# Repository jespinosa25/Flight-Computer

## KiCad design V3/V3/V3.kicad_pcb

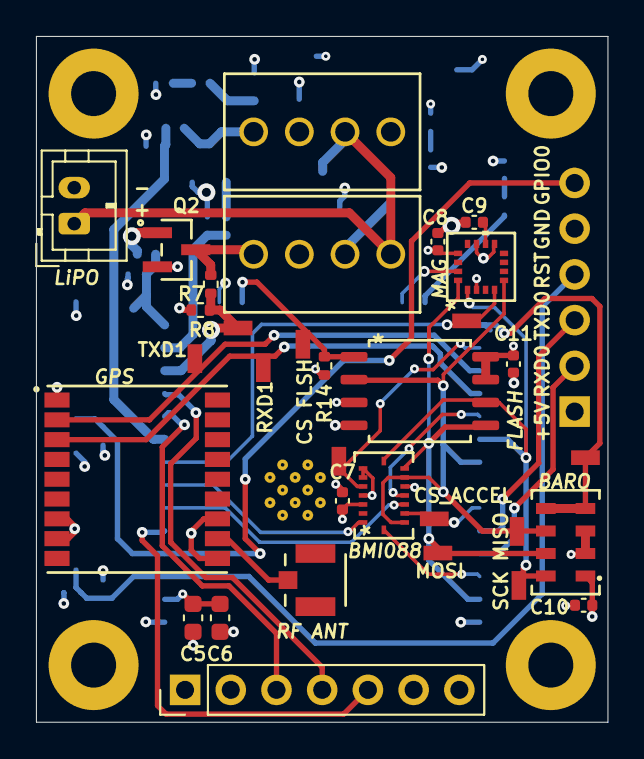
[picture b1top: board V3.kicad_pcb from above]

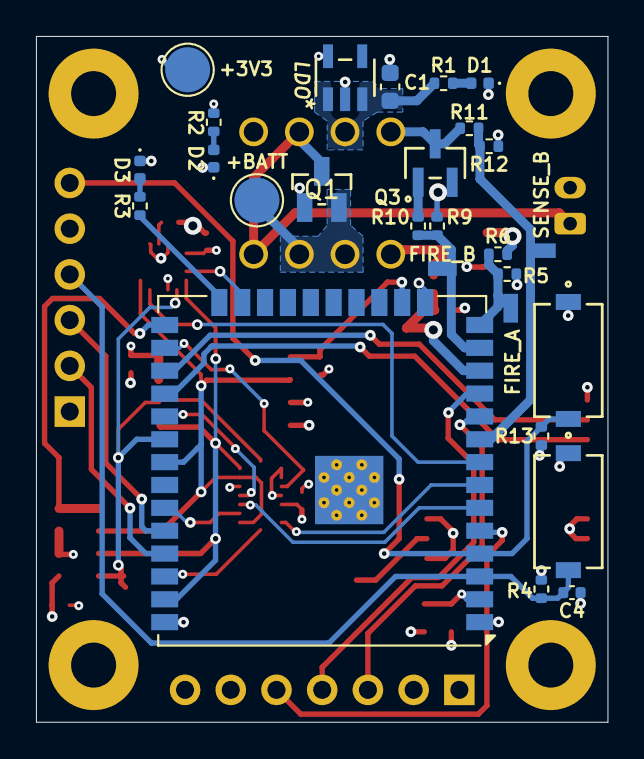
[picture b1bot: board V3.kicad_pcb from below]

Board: 4 copper layers, 31.8 x 38.1 mm, 64 parts (28 on the bottom side), 40 nets.

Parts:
+3V3: TestPoint; TestPoint_Pad_D2.5mm
+BATT: TestPoint; TestPoint_Pad_D2.5mm
BARO: MS560702BA03-50; SON8_MS5611_TEC
BMI088
: BMI088; QFN_BMI085_BOS
BT1: LiPO; JST_PH_B2B-PH-K_1x02_P2.00mm_Vertical
C1: 22uF; C_0603_1608Metric
C4, C8: 1uF; C_0402_1005Metric
C5: 10uF; C_0603_1608Metric
C6: 0.1uF; C_0603_1608Metric
C7, C10, C11: 0.1uF; C_0402_1005Metric
C9: 10uF; C_0402_1005Metric
D1: RED; LED_0402_1005Metric
D2: GREEN; LED_0402_1005Metric
D3: BLUE; LED_0402_1005Metric
FLASH: W25Q16JVSSIQ; W25Q16JVSSIQ_WIN
GPS: MAX-M10M-00B; MOD18_MAX-M10M_UBL
H1, H2, H3, H4: MountingHole_Pad; MountingHole_2.5mm_Pad
J1, J2: Conn_01x04_Pin; CONN_1725672_PXC
J3: Conn_01x06_Pin; PinSocket_1x06_P2.54mm_Vertical
J4: Conn_01x07_Pin; PinHeader_1x07_P2.54mm_Vertical
J5: 2337019-1; CONN_2337019-1_TEC
LDO: LD2980ABM33TR; SOT23-5L_STM
MAG: MMC5983MA; MMC5983MA_MEM
Q1: DMP3099L-7; DMP3099L-7_DIO
Q2, Q3: NMOS; SOT-23_MCC-M
R1: 110; R_0402_1005Metric
R2, R3: 50; R_0402_1005Metric
R4, R13, R14: 10k; R_0402_1005Metric
R5, R7, R9, R11: 100k; R_0402_1005Metric
R6, R10: 1k; R_0402_1005Metric
R8, R12: 27k; R_0402_1005Metric
SW1, SW2: PTS636 SM50J SMTR LFS; SW_PTS636_CNK
TP3, TP4, TP5, TP6, TP7, TP8, TP9, TP10, TP11, TP12, TP13, TP14, TP16, TP17: TestPoint; CONN1_RCU-0C_TEC
U3: ESP32-WROOM-32UE

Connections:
+3.3V: +3V3.1, BARO.1 (VDD), BMI088.3 (VDD), BMI088.11 (VDDIO), C5.1, C6.1, C7.1, C8.1, C10.2, C11.1, FLASH.3 (/WP_(IO2)), FLASH.7 (HOLD), FLASH.8 (VIN), GPS.7 (V_IO), GPS.8 (VCC), J4.6, LDO.5 (VOUT), MAG.2 (VDD), MAG.13 (VDDIO), R2.1, R4.2, R13.2, R14.2, U3.2 (VDD)
+BATT: +BATT.1, C1.1, J1.2, J1.3, J2.3, LDO.1 (VIN), LDO.3 (INHIBIT), Q1.2 (S), R1.1
ACCEL_INT_A: BMI088.16 (INT1), U3.36 (IO22)
ACCEL_INT_B: BMI088.1 (INT2), U3.7 (IO35)
CS_ACCEL: BMI088.14 (CSB1), TP10.1, U3.33 (IO21)
CS_BARO: BARO.4 (CSB), BARO.5 (CSB), TP12.1, U3.25 (IO0)
CS_FLASH: FLASH.1 (CS), R14.1, TP14.1, U3.16 (IO13)
CS_GYRO: BMI088.5 (CSB2), TP11.1, U3.26 (IO4)
CS_MAG: MAG.4 (SPI_CS), TP13.1, U3.8 (IO32)
FIRE_A: R5.1, R6.1, TP6.1, U3.14 (IO12)
FIRE_B: R9.1, R10.1, TP7.1, U3.13 (IO14)
GND: BARO.2 (PS), BARO.3 (GND), BMI088.4 (GNDA), BMI088.6 (GNDIO), BMI088.7 (PS), BT1.2 (-), C1.2, C4.2, C5.2, C6.2, C7.2, C8.2, C9.2, C10.1, C11.2, D1.1 (K), D2.1 (K), D3.1 (K), FLASH.4 (GND), GPS.1 (GND), GPS.10 (GND), GPS.12 (GND), H1.1, H2.1, H3.1, H4.1, J2.1, J3.5, J4.1, J4.2, J4.7, LDO.2 (GND), MAG.9 (GND), MAG.11 (GND), Q1.1 (G), Q2.2 (S), Q3.2 (S), R5.2, R8.1, R9.2, R12.1, SW1.1, SW2.1, U3.1 (GND), U3.15 (GND), U3.38 (GND), U3.39 (GND)
GPIO_0: J3.6, R13.1, SW2.2, U3.4 (SENSOR_VP)
GYRO_INT_A: BMI088.12 (INT3), U3.29 (IO5)
GYRO_INT_B: BMI088.13 (INT4), U3.6 (IO34)
MAG_INT: MAG.15 (INT), U3.23 (IO15)
MISO: BARO.6 (SDO), BMI088.10 (SDO2), BMI088.15 (SDO1), FLASH.2 (DO_(IO1)), MAG.5 (SPI_SDO), TP3.1, U3.31 (IO19)
MOSI: BARO.7 (SDI/SDA), BMI088.9 (SDA/SDI), FLASH.5 (DI_(IO0)), MAG.16 (SDA/SPI_SDI), TP4.1, U3.37 (IO23)
MOS_A: J1.4, Q2.3 (D), R7.2
MOS_B: J2.4, Q3.3 (D), R11.2
unnamed: D1.2 (A), R1.2
unnamed: D2.2 (A), R2.2
unnamed: D3.2 (A), R3.2
unnamed: Q2.1 (G), R6.2
unnamed: Q3.1 (G), R10.2
unnamed: GPS.11 (RF_IN), J5.1
unnamed: C9.1, MAG.10 (CAP)
PROGRAM_LED: R3.1, U3.24 (IO2)
RAW_BATT: BT1.1 (+), J1.1, J2.2, Q1.3 (D)
RESET: C4.1, J3.4, R4.1, SW1.2, U3.3 (EN)
RF_INT: J4.5, U3.5 (SENSOR_VN)
RXD0: J3.2, U3.35 (TXD0/IO1)
RXD1: GPS.3 (RXD), TP8.1, U3.28 (IO17)
RXD2: J4.3, U3.10 (IO25)
SCK: BARO.8 (SCLK), BMI088.8 (SCL/SCK), FLASH.6 (CLK), MAG.1 (SCL/SPI_SCK), TP5.1, U3.30 (IO18)
SENSE_A: R7.1, R8.2, TP16.1, U3.12 (IO27)
SENSE_B: R11.1, R12.2, TP17.1, U3.9 (IO33)
TXD0: J3.3, U3.34 (RXD0/IO3)
TXD1: GPS.2 (TXD), TP9.1, U3.27 (IO16)
TXD2: J4.4, U3.11 (IO26)

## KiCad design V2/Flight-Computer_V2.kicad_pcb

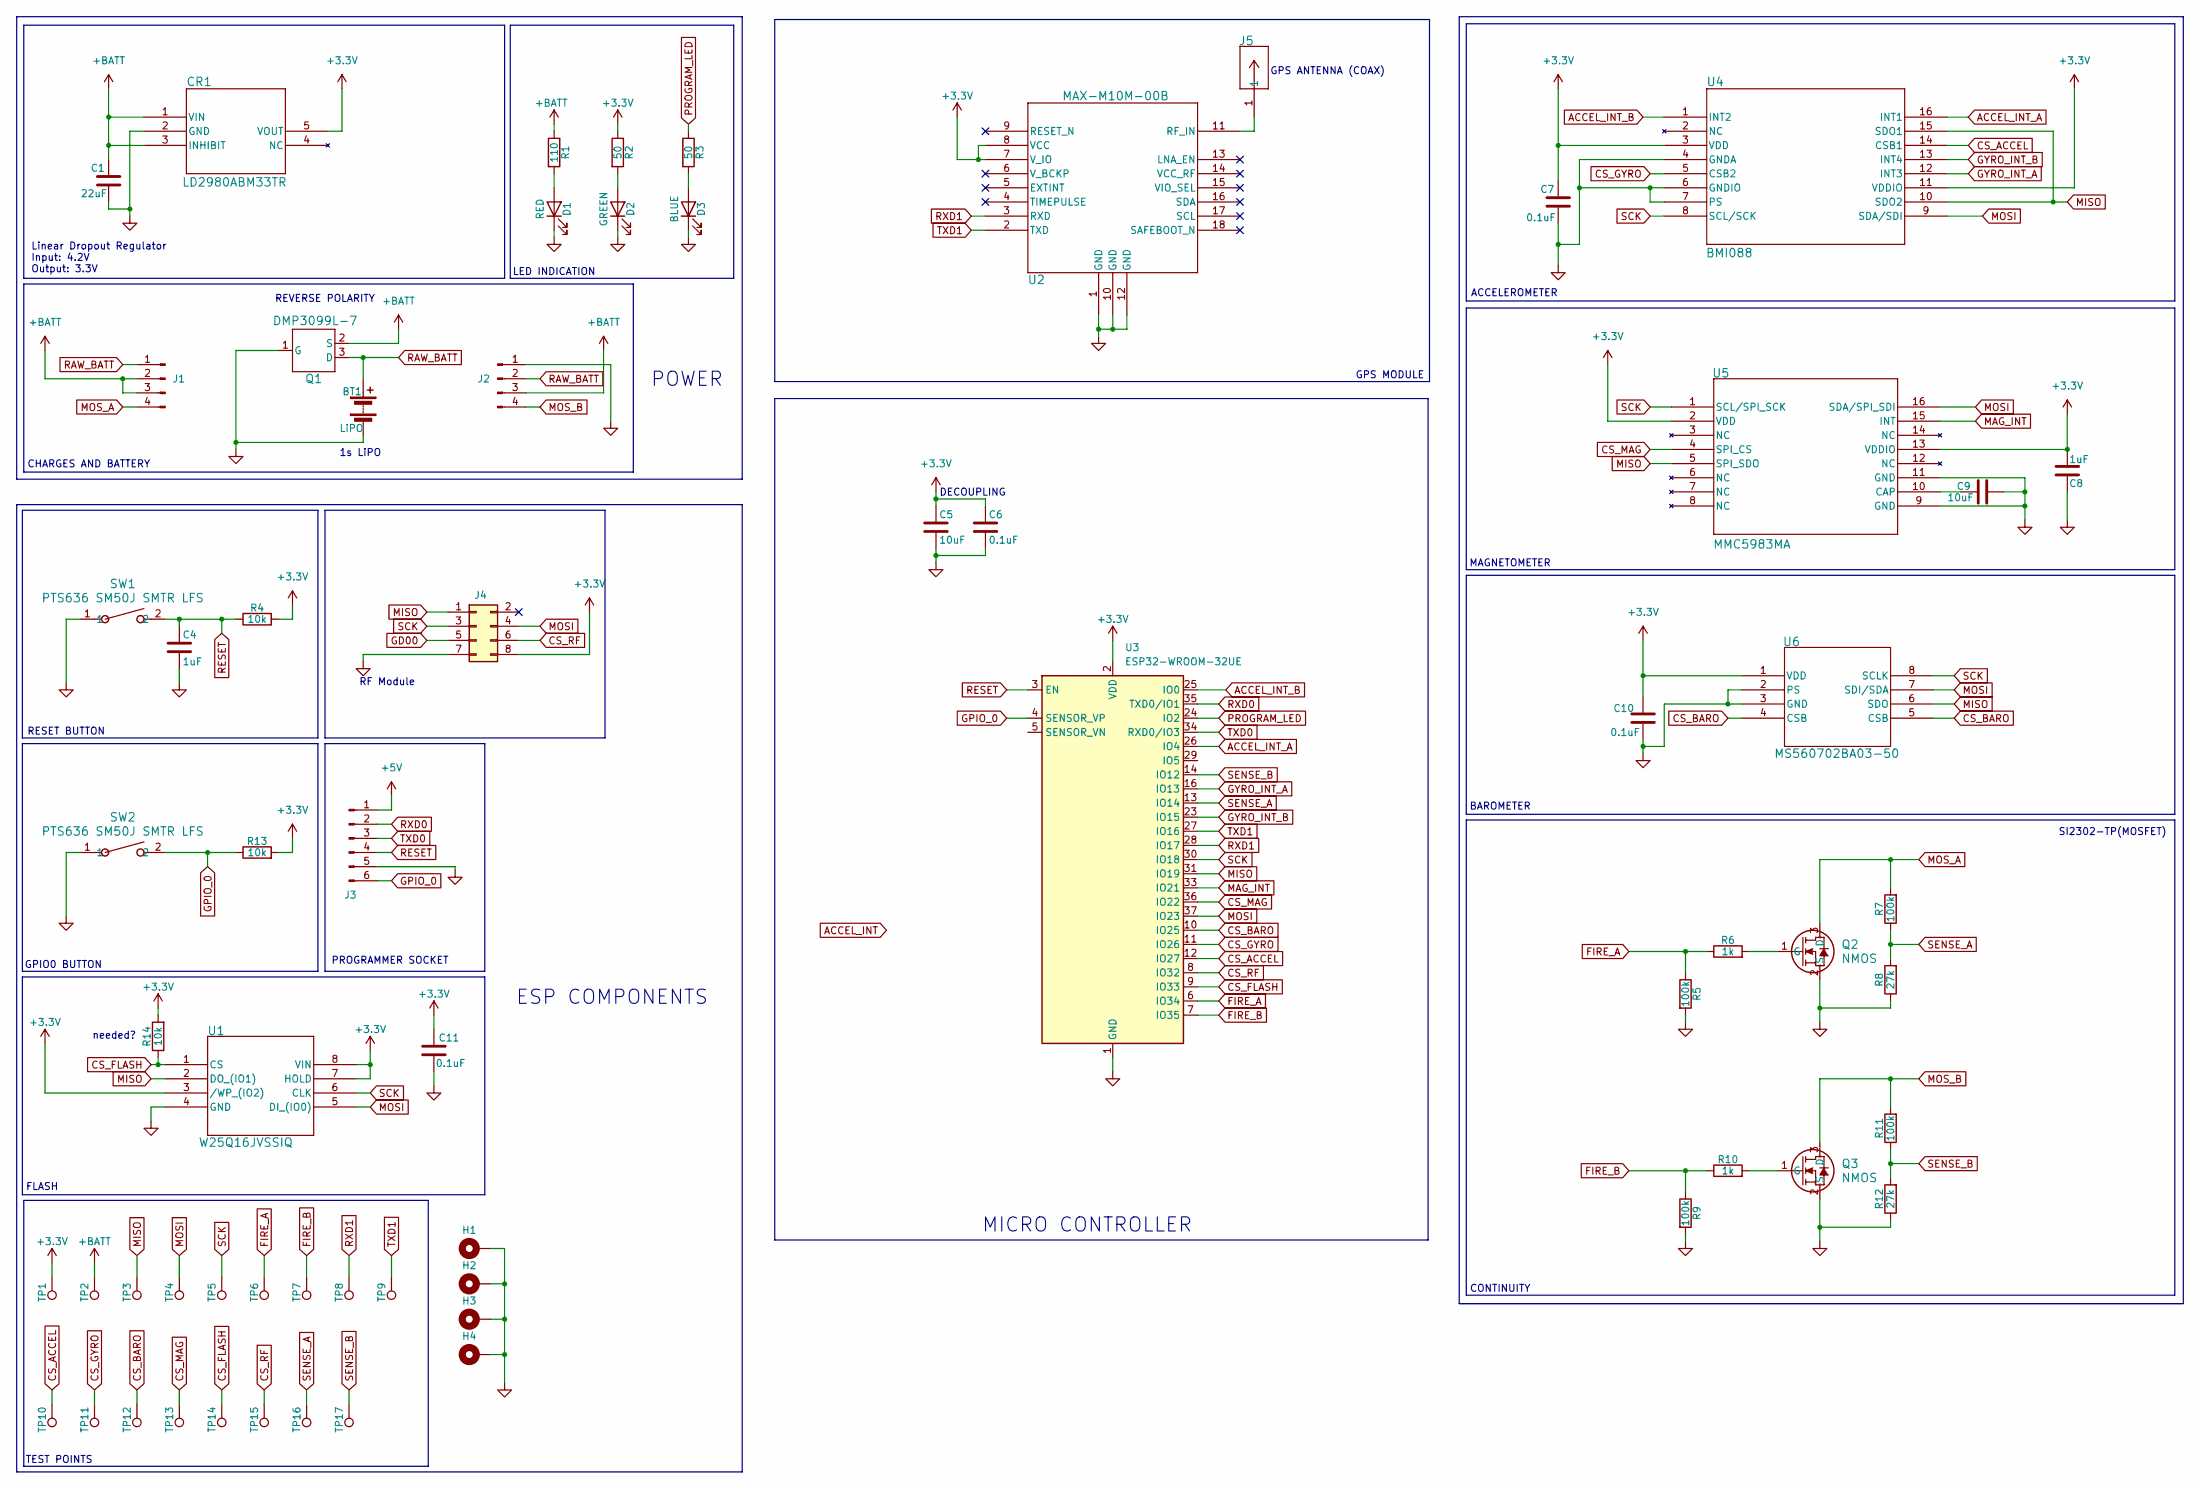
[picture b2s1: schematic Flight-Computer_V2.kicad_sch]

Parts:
BT1: LiPO; JST_PH_B2B-PH-K_1x02_P2.00mm_Vertical
C1: 22uF; C_0603_1608Metric
C4, C8: 1uF; C_0402_1005Metric
C5: 10uF; C_0603_1608Metric
C6: 0.1uF; C_0603_1608Metric
C7, C10, C11: 0.1uF; C_0402_1005Metric
C9: 10uF; C_0402_1005Metric
CR1: LD2980ABM33TR; SOT23-5L_STM
D1: RED; LED_0402_1005Metric
D2: GREEN; LED_0402_1005Metric
D3: BLUE; LED_0402_1005Metric
H1, H2, H3, H4: MountingHole_Pad; MountingHole_2.5mm_Pad
J1, J2: Conn_01x04_Pin; CONN_1725672_PXC
J3: Conn_01x06_Pin; PinSocket_1x06_P2.54mm_Vertical
J4: Conn_02x04_Odd_Even; PinSocket_2x04_P2.54mm_Vertical
J5: 2337019-1; CONN_2337019-1_TEC
Q1: DMP3099L-7; DMP3099L-7_DIO
Q2, Q3: NMOS; SOT-23_MCC-M
R1: 110; R_0402_1005Metric
R2, R3: 50; R_0402_1005Metric
R4, R13, R14: 10k; R_0402_1005Metric
R5, R7, R9, R11: 100k; R_0402_1005Metric
R6, R10: 1k; R_0402_1005Metric
R8, R12: 27k; R_0402_1005Metric
SW1, SW2: PTS636 SM50J SMTR LFS; SW_PTS636_CNK
TP1, TP2: TestPoint; TestPoint_Pad_D2.5mm
TP3, TP4, TP5, TP6, TP7, TP8, TP9, TP10, TP11, TP12, TP13, TP14, TP15, TP16, TP17: TestPoint; TestPoint_Loop_D2.60mm_Drill1.6mm_Beaded
U1: W25Q16JVSSIQ; W25Q16JVSSIQ_WIN
U2: MAX-M10M-00B; MOD18_MAX-M10M_UBL
U3: ESP32-WROOM-32UE
U4: BMI088; QFN_BMI085_BOS
U5: MMC5983MA; MMC5983MA_MEM
U6: MS560702BA03-50; SON8_MS5611_TEC

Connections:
+3.3V: C5.1, C6.1, C7.1, C8.1, C10.2, C11.1, CR1.5 (VOUT), J4.8, R2.1, R4.2, R13.2, R14.2, TP1.1, U1.3 (/WP_(IO2)), U1.7 (HOLD), U1.8 (VIN), U2.7 (V_IO), U2.8 (VCC), U3.2 (VDD), U4.3 (VDD), U4.11 (VDDIO), U5.2 (VDD), U5.13 (VDDIO), U6.1 (VDD)
+5V: J3.1
+BATT: C1.1, CR1.1 (VIN), CR1.3 (INHIBIT), J1.2, J1.3, J2.3, Q1.2 (S), R1.1, TP2.1
ACCEL_INT_A: U3.26 (IO4), U4.16 (INT1)
ACCEL_INT_B: U3.25 (IO0), U4.1 (INT2)
CS_ACCEL: TP10.1, U3.12 (IO27), U4.14 (CSB1)
CS_BARO: TP12.1, U3.10 (IO25), U6.4 (CSB), U6.5 (CSB)
CS_FLASH: R14.1, TP14.1, U1.1 (CS), U3.9 (IO33)
CS_GYRO: TP11.1, U3.11 (IO26), U4.5 (CSB2)
CS_MAG: TP13.1, U3.36 (IO22), U5.4 (SPI_CS)
CS_RF: J4.6, TP15.1, U3.8 (IO32)
FIRE_A: R5.1, R6.1, TP6.1, U3.6 (IO34)
FIRE_B: R9.1, R10.1, TP7.1, U3.7 (IO35)
GD00: J4.5
GND: BT1.2 (-), C1.2, C4.2, C5.2, C6.2, C7.2, C8.2, C9.2, C10.1, C11.2, CR1.2 (GND), D1.1 (K), D2.1 (K), D3.1 (K), H1.1, H2.1, H3.1, H4.1, J2.1, J3.5, J4.7, Q1.1 (G), Q2.2 (S), Q3.2 (S), R5.2, R8.1, R9.2, R12.1, SW1.1, SW2.1, U1.4 (GND), U2.1 (GND), U2.10 (GND), U2.12 (GND), U3.1 (GND), U3.15 (GND), U3.38 (GND), U3.39 (GND), U4.4 (GNDA), U4.6 (GNDIO), U4.7 (PS), U5.9 (GND), U5.11 (GND), U6.2 (PS), U6.3 (GND)
GPIO_0: J3.6, R13.1, SW2.2, U3.4 (SENSOR_VP)
GYRO_INT_A: U3.16 (IO13), U4.12 (INT3)
GYRO_INT_B: U3.23 (IO15), U4.13 (INT4)
MAG_INT: U3.33 (IO21), U5.15 (INT)
MISO: J4.1, TP3.1, U1.2 (DO_(IO1)), U3.31 (IO19), U4.10 (SDO2), U4.15 (SDO1), U5.5 (SPI_SDO), U6.6 (SDO)
MOSI: J4.4, TP4.1, U1.5 (DI_(IO0)), U3.37 (IO23), U4.9 (SDA/SDI), U5.16 (SDA/SPI_SDI), U6.7 (SDI/SDA)
MOS_A: J1.4, Q2.3 (D), R7.2
MOS_B: J2.4, Q3.3 (D), R11.2
unnamed: D1.2 (A), R1.2
unnamed: D2.2 (A), R2.2
unnamed: D3.2 (A), R3.2
unnamed: Q2.1 (G), R6.2
unnamed: Q3.1 (G), R10.2
unnamed: J5.1, U2.11 (RF_IN)
unnamed: C9.1, U5.10 (CAP)
PROGRAM_LED: R3.1, U3.24 (IO2)
RAW_BATT: BT1.1 (+), J1.1, J2.2, Q1.3 (D)
RESET: C4.1, J3.4, R4.1, SW1.2, U3.3 (EN)
RXD0: J3.2, U3.35 (TXD0/IO1)
RXD1: TP8.1, U2.3 (RXD), U3.28 (IO17)
SCK: J4.3, TP5.1, U1.6 (CLK), U3.30 (IO18), U4.8 (SCL/SCK), U5.1 (SCL/SPI_SCK), U6.8 (SCLK)
SENSE_A: R7.1, R8.2, TP16.1, U3.13 (IO14)
SENSE_B: R11.1, R12.2, TP17.1, U3.14 (IO12)
TXD0: J3.3, U3.34 (RXD0/IO3)
TXD1: TP9.1, U2.2 (TXD), U3.27 (IO16)

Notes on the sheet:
BAROMETER
LED INDICATION
1s LiPO
TEST POINTS
PROGRAMMER SOCKET
GPS ANTENNA (COAX)
ACCELEROMETER
needed?
RF Module
Linear Dropout Regulator Input: 4.2V Output: 3.3V
GPS MODULE
ESP COMPONENTS
FLASH
GPIO0 BUTTON
POWER
RESET BUTTON
CONTINUITY
SI2302-TP(MOSFET)
DECOUPLING
REVERSE POLARITY
CHARGES AND BATTERY
MAGNETOMETER
MICRO CONTROLLER

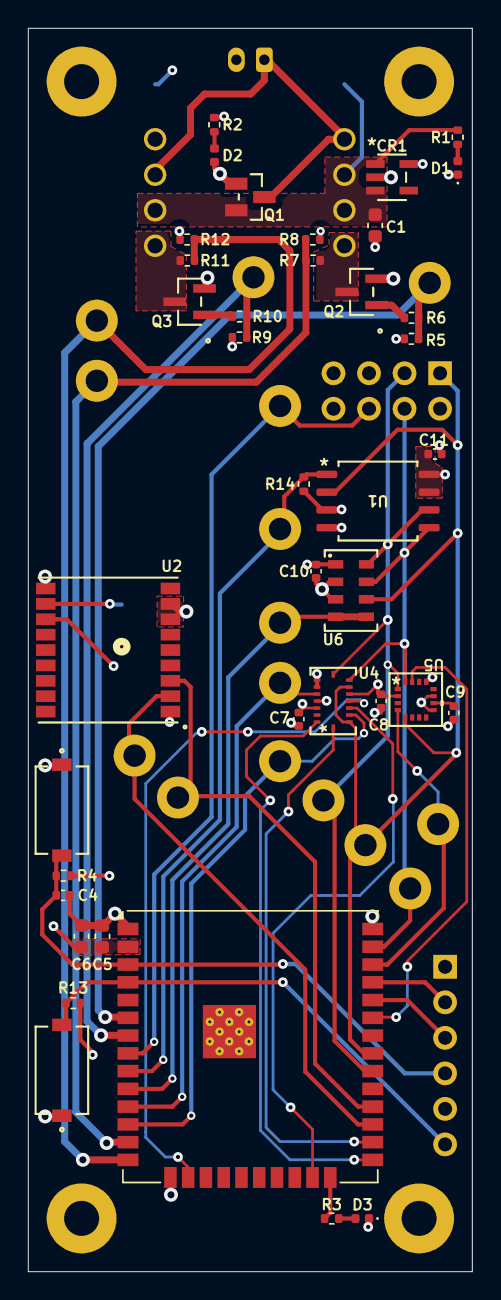
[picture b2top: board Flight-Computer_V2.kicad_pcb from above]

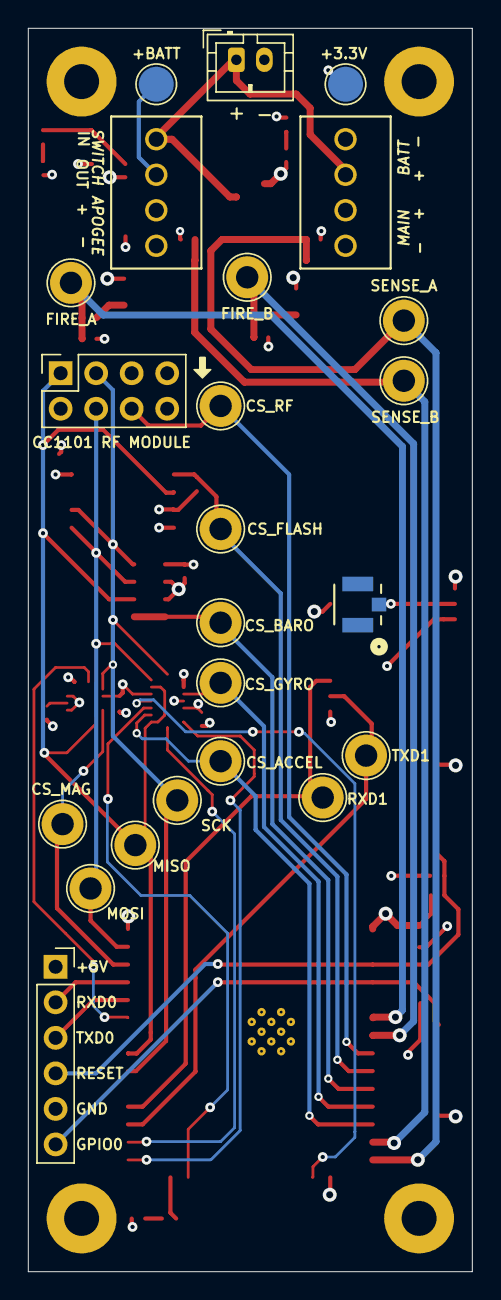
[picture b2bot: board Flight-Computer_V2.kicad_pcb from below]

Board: 4 copper layers, 31.8 x 88.9 mm, 65 parts (23 on the bottom side), 38 nets.

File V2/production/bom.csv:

Designator,Footprint,Quantity,Value,LCSC Part #
BT1,JST_PH_B2B-PH-K_1x02_P2.00mm_Vertical,1,LiPO,
C1,0201,1,22uF,
"C10, C11, C6, C7",0201,4,0.1uF,
"C4, C8",0201,2,1uF,
"C5, C9",0201,2,10uF,
CR1,SOT23-5L_STM,1,LD2980ABM33TR,
D1,0201,1,RED,
D2,0201,1,GREEN,
D3,0201,1,BLUE,
GPS_ANT,Pin_D1.0mm_L10.0mm,1,Pin_D1.0mm_L10.0mm,
IC1,ESP32S2MINI2N4R2,1,ESP32-S2-MINI-2-N4R2,
"J1, J2",CONN_1725672_PXC,2,Conn_01x04_Pin,
J3,PinSocket_1x06_P2.54mm_Vertical,1,Conn_01x06_Pin,
J4,PinSocket_2x04_P2.54mm_Vertical,1,Conn_02x04_Odd_Even,
Q1,DMP3099L-7_DIO,1,PMOS,
"Q2, Q3",SOT-23_MCC,2,NMOS,
R1,0201,1,110,
"R10, R6",0201,2,1k,
"R11, R5, R7, R9",0201,4,100k,
"R12, R8",0201,2,27k,
"R2, R3",0201,2,50,
R4,0201,1,10k,
SW1,SW_PTS636_CNK,1,PTS636 SM50J SMTR LFS,
"TP1, TP2",TestPoint_Pad_D2.5mm,2,TestPoint,
"TP10, TP11, TP12, TP14, TP15, TP3, TP4, TP5, TP6, TP7, TP8, TP9",TestPoint_Loop_D1.80mm_Drill1.0mm_Beaded,12,TestPoint,
U1,W25Q16JVSSIQ_WIN,1,W25Q16JVSSIQ,
U2,MOD18_MAX-M10M_UBL,1,MAX-M10M-00B,
U4,QFN_BMI085_BOS,1,BMI088,
U5,MMC5983MA_MEM,1,MMC5983MA,
U6,SON8_MS5611_TEC,1,MS560702BA03-50,

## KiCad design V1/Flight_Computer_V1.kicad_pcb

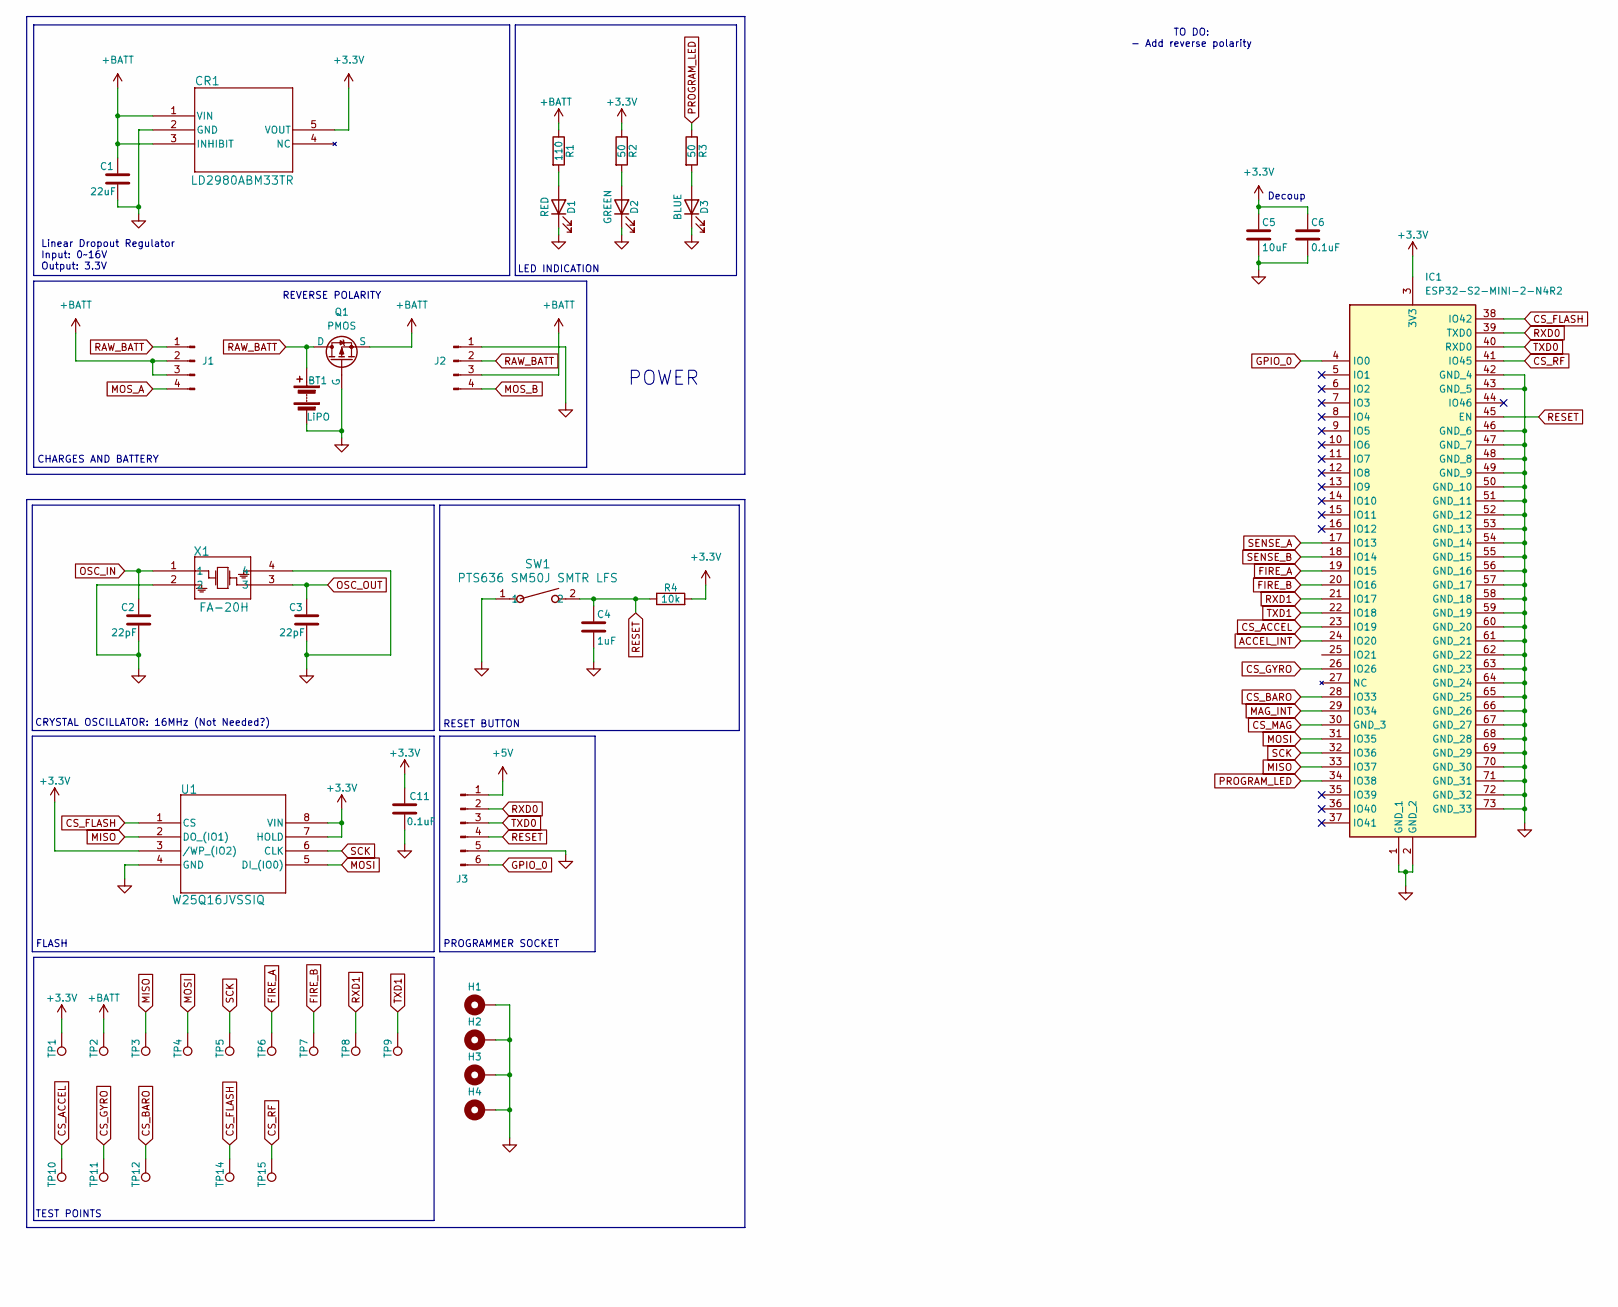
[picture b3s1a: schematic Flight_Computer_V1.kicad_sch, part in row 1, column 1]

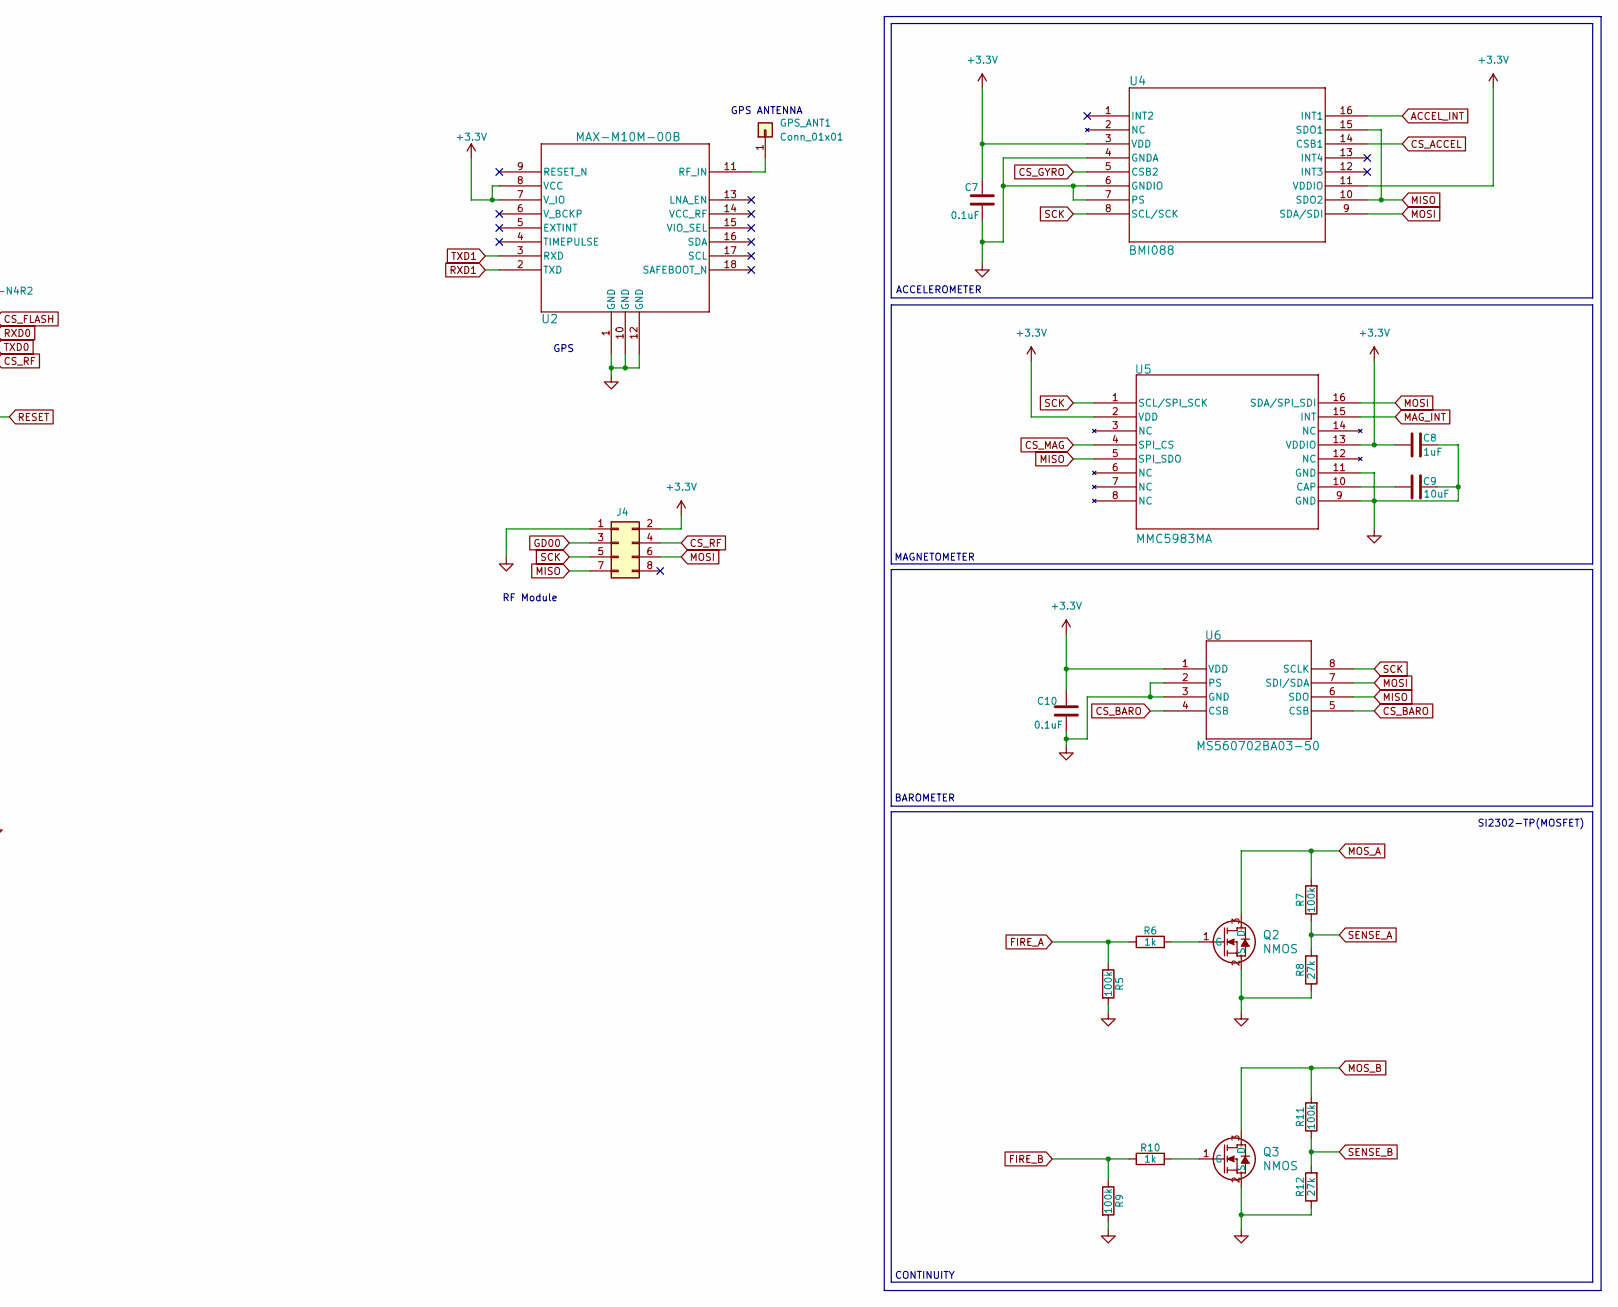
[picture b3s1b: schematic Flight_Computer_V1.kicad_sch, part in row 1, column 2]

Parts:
BT1: LiPO; JST_PH_B2B-PH-K_1x02_P2.00mm_Vertical
C1: 22uF; C_0201_0603Metric
C2, C3: 22pF; C_0201_0603Metric
C4, C8: 1uF; C_0201_0603Metric
C5, C9: 10uF; C_0201_0603Metric
C6, C7, C10, C11: 0.1uF; C_0201_0603Metric
CR1: LD2980ABM33TR; SOT23-5L_STM
D1: RED; LED_0201_0603Metric
D2: GREEN; LED_0201_0603Metric
D3: BLUE; LED_0201_0603Metric
GPS_ANT1: Conn_01x01
H1, H2, H3, H4: MountingHole_Pad; MountingHole_2.5mm_Pad
IC1: ESP32-S2-MINI-2-N4R2; ESP32S2MINI2N4R2; Mouser Part Number 356-ESP32MINI-2-N4R2
J1, J2: Conn_01x04_Pin; CONN_1725672_PXC
J3: Conn_01x06_Pin; PinSocket_1x06_P2.54mm_Vertical
J4: Conn_02x04_Odd_Even; PinSocket_2x04_P2.54mm_Vertical
Q1: PMOS; DMP3099L-7_DIO
Q2, Q3: NMOS; SOT-23_MCC
R1: 110; R_0201_0603Metric
R2, R3: 50; R_0201_0603Metric
R4: 10k; R_0201_0603Metric
R5, R7, R9, R11: 100k; R_0201_0603Metric
R6, R10: 1k; R_0201_0603Metric
R8, R12: 27k; R_0201_0603Metric
SW1: PTS636 SM50J SMTR LFS; SW_PTS636_CNK
TP1, TP2: TestPoint; TestPoint_Pad_D2.5mm
TP3, TP4, TP5, TP6, TP7, TP8, TP9, TP10, TP11, TP12, TP14, TP15: TestPoint; TestPoint_Loop_D1.80mm_Drill1.0mm_Beaded
U1: W25Q16JVSSIQ; W25Q16JVSSIQ_WIN
U2: MAX-M10M-00B; MOD18_MAX-M10M_UBL
U4: BMI088; QFN_BMI085_BOS
U5: MMC5983MA; MMC5983MA_MEM
U6: MS560702BA03-50; SON8_MS5611_TEC
X1: FA-20H; XTAL4P_FA-20H_EPS

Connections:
+3.3V: C5.1, C6.1, C7.1, C8.1, C10.2, C11.1, CR1.5 (VOUT), IC1.3 (3V3), J4.2, R2.1, R4.2, TP1.1, U1.3 (/WP_(IO2)), U1.7 (HOLD), U1.8 (VIN), U2.7 (V_IO), U2.8 (VCC), U4.3 (VDD), U4.11 (VDDIO), U5.2 (VDD), U5.13 (VDDIO), U6.1 (VDD)
+5V: J3.1
+BATT: C1.1, CR1.1 (VIN), CR1.3 (INHIBIT), J1.2, J1.3, J2.3, Q1.2 (S), R1.1, TP2.1
ACCEL_INT: IC1.24 (IO20), U4.16 (INT1)
CS_ACCEL: IC1.23 (IO19), TP10.1, U4.14 (CSB1)
CS_BARO: IC1.28 (IO33), TP12.1, U6.4 (CSB), U6.5 (CSB)
CS_FLASH: IC1.38 (IO42), TP14.1, U1.1 (CS)
CS_GYRO: IC1.26 (IO26), TP11.1, U4.5 (CSB2)
CS_MAG: IC1.30 (GND_3), U5.4 (SPI_CS)
CS_RF: IC1.41 (IO45), J4.4, TP15.1
FIRE_A: IC1.19 (IO15), R5.1, R6.1, TP6.1
FIRE_B: IC1.20 (IO16), R9.1, R10.1, TP7.1
GD00: J4.3
GND: BT1.2 (-), C1.2, C2.2, C3.2, C4.2, C5.2, C6.2, C7.2, C8.2, C9.2, C10.1, C11.2, CR1.2 (GND), D1.1 (K), D2.1 (K), D3.1 (K), H1.1, H2.1, H3.1, H4.1, IC1.1 (GND_1), IC1.2 (GND_2), IC1.42 (GND_4), IC1.43 (GND_5), IC1.46 (GND_6), IC1.47 (GND_7), IC1.48 (GND_8), IC1.49 (GND_9), IC1.50 (GND_10), IC1.51 (GND_11), IC1.52 (GND_12), IC1.53 (GND_13), IC1.54 (GND_14), IC1.55 (GND_15), IC1.56 (GND_16), IC1.57 (GND_17), IC1.58 (GND_18), IC1.59 (GND_19), IC1.60 (GND_20), IC1.61 (GND_21), IC1.62 (GND_22), IC1.63 (GND_23), IC1.64 (GND_24), IC1.65 (GND_25), IC1.66 (GND_26), IC1.67 (GND_27), IC1.68 (GND_28), IC1.69 (GND_29), IC1.70 (GND_30), IC1.71 (GND_31), IC1.72 (GND_32), IC1.73 (GND_33), J2.1, J3.5, J4.1, Q1.1 (G), Q2.2 (S), Q3.2 (S), R5.2, R8.1, R9.2, R12.1, SW1.1, U1.4 (GND), U2.1 (GND), U2.10 (GND), U2.12 (GND), U4.4 (GNDA), U4.6 (GNDIO), U4.7 (PS), U5.9 (GND), U5.11 (GND), U6.2 (PS), U6.3 (GND), X1.2, X1.4
GPIO_0: IC1.4 (IO0), J3.6
MAG_INT: IC1.29 (IO34), U5.15 (INT)
MISO: IC1.33 (IO37), J4.7, TP3.1, U1.2 (DO_(IO1)), U4.10 (SDO2), U4.15 (SDO1), U5.5 (SPI_SDO), U6.6 (SDO)
MOSI: IC1.31 (IO35), J4.6, TP4.1, U1.5 (DI_(IO0)), U4.9 (SDA/SDI), U5.16 (SDA/SPI_SDI), U6.7 (SDI/SDA)
MOS_A: J1.4, Q2.3 (D), R7.2
MOS_B: J2.4, Q3.3 (D), R11.2
unnamed: C2.1, X1.1
unnamed: C3.1, X1.3
unnamed: D1.2 (A), R1.2
unnamed: D2.2 (A), R2.2
unnamed: D3.2 (A), R3.2
unnamed: GPS_ANT1.1, U2.11 (RF_IN)
unnamed: Q2.1 (G), R6.2
unnamed: Q3.1 (G), R10.2
unnamed: C9.1, U5.10 (CAP)
PROGRAM_LED: IC1.34 (IO38), R3.1
RAW_BATT: BT1.1 (+), J1.1, J2.2, Q1.3 (D)
RESET: C4.1, IC1.45 (EN), J3.4, R4.1, SW1.2
RXD0: IC1.39 (TXD0), J3.2
RXD1: IC1.21 (IO17), TP8.1, U2.2 (TXD)
SCK: IC1.32 (IO36), J4.5, TP5.1, U1.6 (CLK), U4.8 (SCL/SCK), U5.1 (SCL/SPI_SCK), U6.8 (SCLK)
SENSE_A: IC1.17 (IO13), R7.1, R8.2
SENSE_B: IC1.18 (IO14), R11.1, R12.2
TXD0: IC1.40 (RXD0), J3.3
TXD1: IC1.22 (IO18), TP9.1, U2.3 (RXD)

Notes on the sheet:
BAROMETER
LED INDICATION
TEST POINTS
PROGRAMMER SOCKET
GPS ANTENNA
ACCELEROMETER
RF Module
Linear Dropout Regulator Input: 0~16V Output: 3.3V
GPS
FLASH
CRYSTAL OSCILLATOR: 16MHz (Not Needed?)
POWER
TO DO: - Add reverse polarity
RESET BUTTON
CONTINUITY
SI2302-TP(MOSFET)
Decoup
REVERSE POLARITY
CHARGES AND BATTERY
MAGNETOMETER

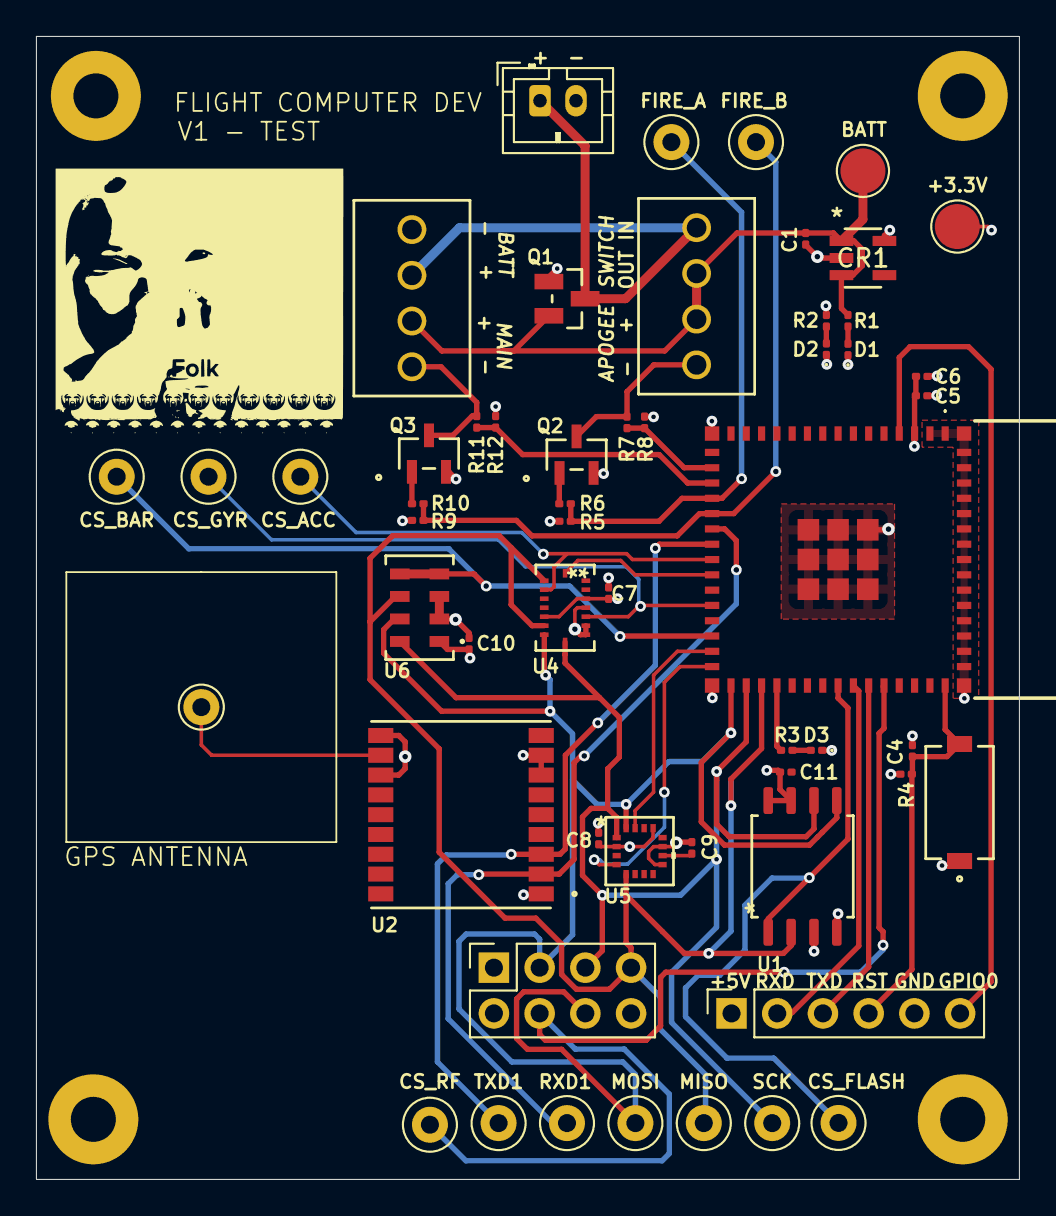
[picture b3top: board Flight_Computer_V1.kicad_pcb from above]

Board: 4 copper layers, 54.6 x 63.5 mm, 59 parts (0 on the bottom side), 34 nets.

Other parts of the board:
GPS_ANT: Pin_D1.0mm_L10.0mm

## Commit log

2025-10-12 reorg
2025-10-16 GPS, RF Receiver
2026-01-01 V1 for review
2026-01-22 V2 changes
2026-01-23 v2 cahnges
2026-01-27 V2 finalized
2026-02-14 V3 Changes
